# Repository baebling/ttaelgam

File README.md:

# ttaelgam
custom keyboard design

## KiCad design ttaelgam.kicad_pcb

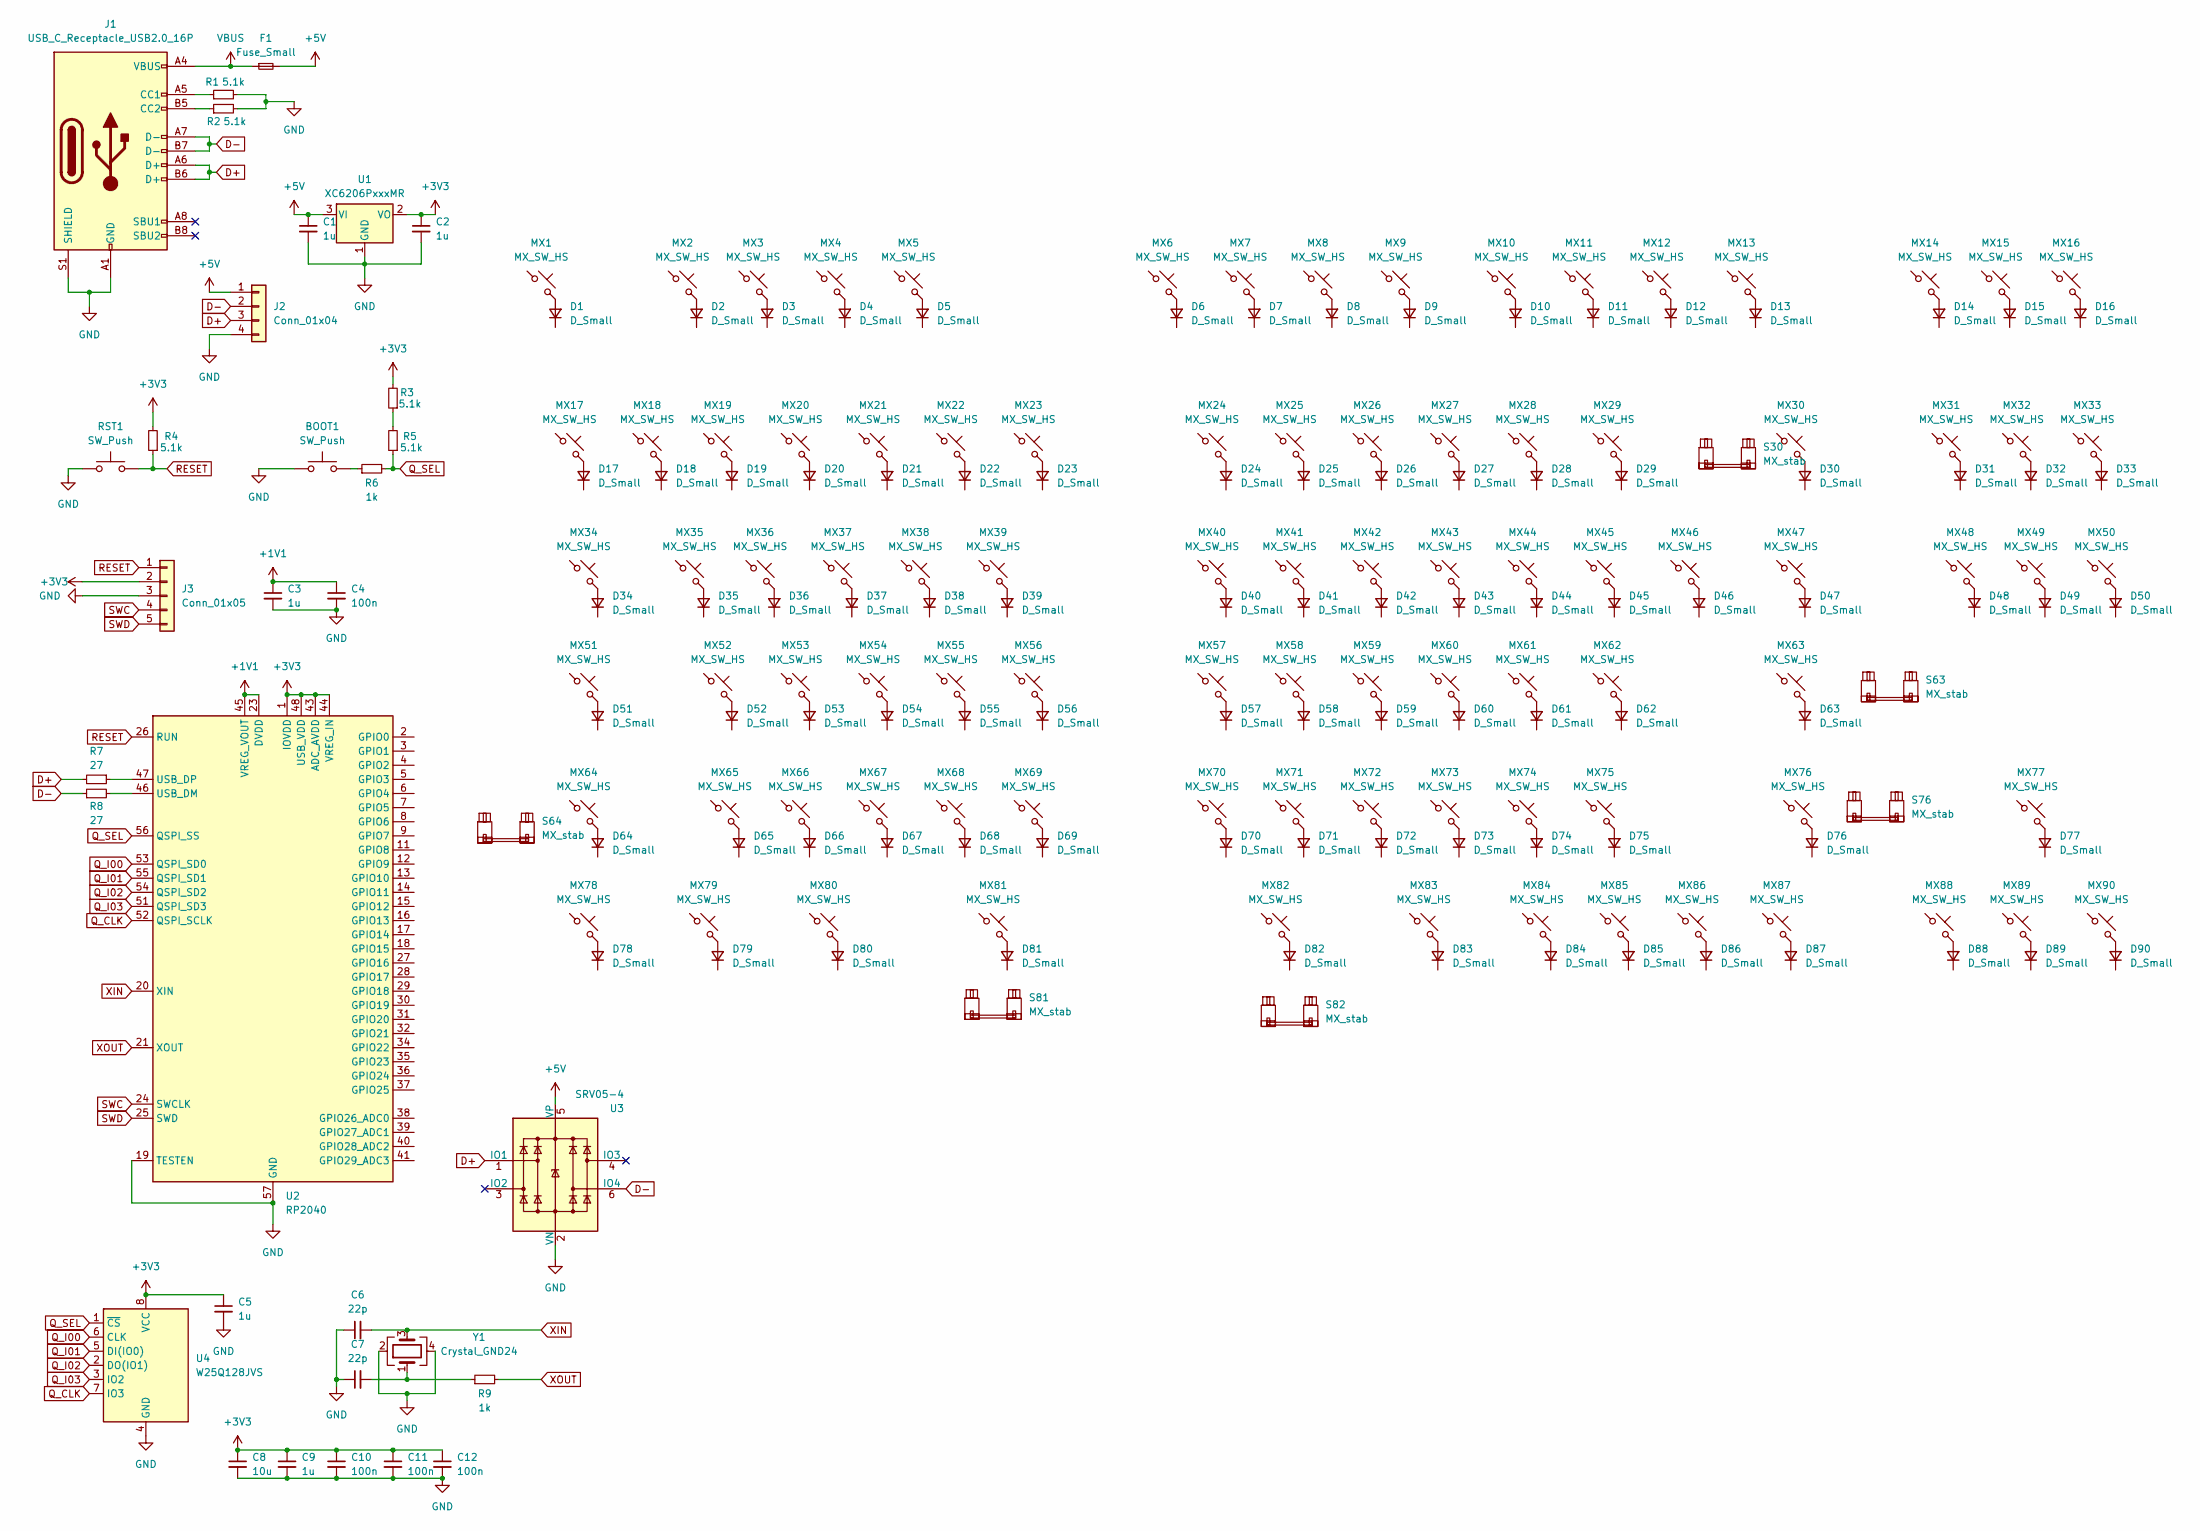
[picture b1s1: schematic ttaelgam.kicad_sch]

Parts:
BOOT1: SW_Push; SW_SPST_TL3342
C1, C2, C3, C5, C9: 1u; C_0402_1005Metric
C4, C10, C11, C12: 100n; C_0402_1005Metric
C6, C7: 22p; C_0402_1005Metric
C8: 10u; C_0603_1608Metric
D1, D2, D3, D4, D5, D6, D7, D8, D9, D10, D11, D12, D13, D14, D15, D16, D17, D18, D19, D20, D21, D22, D23, D24, D25, D26, D27, D28, D29, D30, D31, D32, D33, D34, D35, D36, D37, D38, D39, D40, D41, D42, D43, D44, D45, D46, D47, D48, D49, D50, D51, D52, D53, D54, D55, D56, D57, D58, D59, D60, D61, D62, D63, D64, D65, D66, D67, D68, D69, D70, D71, D72, D73, D74, D75, D76, D77, D78, D79, D80, D81, D82, D83, D84, D85, D86, D87, D88, D89, D90: D_Small; D_SOD-123
F1: Fuse_Small; Fuse_1206_3216Metric
J1: USB_C_Receptacle_USB2.0_16P; USB_C_Receptacle_HRO_TYPE-C-31-M-12
J2: Conn_01x04; JST_SH_SM04B-SRSS-TB_1x04-1MP_P1.00mm_Horizontal
J3: Conn_01x05; PinHeader_1x05_P2.54mm_Vertical
MX1, MX2, MX3, MX4, MX5, MX6, MX7, MX8, MX9, MX10, MX11, MX12, MX13, MX14, MX15, MX16, MX17, MX18, MX19, MX20, MX21, MX22, MX23, MX24, MX25, MX26, MX27, MX28, MX29, MX30, MX31, MX32, MX33, MX35, MX36, MX37, MX38, MX39, MX40, MX41, MX42, MX43, MX44, MX45, MX46, MX48, MX49, MX50, MX52, MX53, MX54, MX55, MX56, MX57, MX58, MX59, MX60, MX61, MX62, MX63, MX64, MX65, MX66, MX67, MX68, MX69, MX70, MX71, MX72, MX73, MX74, MX75, MX76, MX77, MX81, MX82, MX84, MX85, MX86, MX87, MX88, MX89, MX90: MX_SW_HS; SW_MX_HS_CPG151101S11_1u
MX34, MX47: MX_SW_HS; SW_MX_HS_CPG151101S11_1.5u
MX51: MX_SW_HS; SW_MX_HS_CPG151101S11_1.75u_STP_1.25
MX78, MX79, MX80, MX83: MX_SW_HS; SW_MX_HS_CPG151101S11_1.25u
R1, R2, R3, R4, R5: 5.1k; R_0402_1005Metric
R6, R9: 1k; R_0402_1005Metric
R7, R8: 27; R_0402_1005Metric
RST1: SW_Push; SW_SPST_TL3342
S30: MX_stab; STAB_MX_2u
S63, S64: MX_stab; STAB_MX_2.25u
S76, S81: MX_stab; STAB_MX_2.75u
S82: MX_stab; STAB_MX_3u
U1: XC6206PxxxMR; SOT-23-3
U2: RP2040; QFN-56-1EP_7x7mm_P0.4mm_EP3.2x3.2mm
U3: SRV05-4; SOT-23-6
U4: W25Q128JVS; SOIC-8_5.23x5.23mm_P1.27mm
Y1: Crystal_GND24; Crystal_SMD_3225-4Pin_3.2x2.5mm

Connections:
+1V1: C3.1, C4.1, U2.23 (DVDD), U2.45 (VREG_VOUT), U2.50 (DVDD)
+3V3: C2.1, C5.1, C8.1, C9.1, C10.1, C11.1, C12.1, J3.2, R3.2, R4.2, U1.2 (VO), U2.1 (IOVDD), U2.10 (IOVDD), U2.22 (IOVDD), U2.33 (IOVDD), U2.42 (IOVDD), U2.43 (ADC_AVDD), U2.44 (VREG_IN), U2.48 (USB_VDD), U2.49 (IOVDD), U4.8 (VCC)
+5V: C1.1, F1.2, J2.1, U1.3 (VI), U3.5 (VP)
D+: J1.A6 (D+), J1.B6 (D+), J2.3, R7.2, U3.1 (IO1)
D-: J1.A7 (D-), J1.B7 (D-), J2.2, R8.1, U3.6 (IO4)
GND: BOOT1.1, C1.2, C2.2, C3.2, C4.2, C5.2, C6.1, C7.1, C8.2, C9.2, C10.2, C11.2, C12.2, J1.A1 (GND), J1.A12 (GND), J1.B1 (GND), J1.B12 (GND), J1.S1 (SHIELD), J2.4, J3.3, R1.2, R2.2, RST1.1, U1.1 (GND), U2.19 (TESTEN), U2.57 (GND), U3.2 (VN), U4.4 (GND), Y1.2, Y1.4
unnamed: BOOT1.2, R6.1
unnamed: C7.2, R9.1, Y1.1
unnamed: D1.2 (A), MX1.2
unnamed: D2.2 (A), MX2.2
unnamed: D3.2 (A), MX3.2
unnamed: D4.2 (A), MX4.2
unnamed: D5.2 (A), MX5.2
unnamed: D6.2 (A), MX6.2
unnamed: D7.2 (A), MX7.2
unnamed: D8.2 (A), MX8.2
unnamed: D9.2 (A), MX9.2
unnamed: D10.2 (A), MX10.2
unnamed: D11.2 (A), MX11.2
unnamed: D12.2 (A), MX12.2
unnamed: D13.2 (A), MX13.2
unnamed: D14.2 (A), MX14.2
unnamed: D15.2 (A), MX15.2
unnamed: D16.2 (A), MX16.2
unnamed: D17.2 (A), MX17.2
unnamed: D18.2 (A), MX18.2
unnamed: D19.2 (A), MX19.2
unnamed: D20.2 (A), MX20.2
unnamed: D21.2 (A), MX21.2
unnamed: D22.2 (A), MX22.2
unnamed: D23.2 (A), MX23.2
unnamed: D24.2 (A), MX24.2
unnamed: D25.2 (A), MX25.2
unnamed: D26.2 (A), MX26.2
unnamed: D27.2 (A), MX27.2
unnamed: D28.2 (A), MX28.2
unnamed: D29.2 (A), MX29.2
unnamed: D30.2 (A), MX30.2
unnamed: D31.2 (A), MX31.2
unnamed: D32.2 (A), MX32.2
unnamed: D33.2 (A), MX33.2
unnamed: D34.2 (A), MX34.2
unnamed: D35.2 (A), MX35.2
unnamed: D36.2 (A), MX36.2
unnamed: D37.2 (A), MX37.2
unnamed: D38.2 (A), MX38.2
unnamed: D39.2 (A), MX39.2
unnamed: D40.2 (A), MX40.2
unnamed: D41.2 (A), MX41.2
unnamed: D42.2 (A), MX42.2
unnamed: D43.2 (A), MX43.2
unnamed: D44.2 (A), MX44.2
unnamed: D45.2 (A), MX45.2
unnamed: D46.2 (A), MX46.2
unnamed: D47.2 (A), MX47.2
unnamed: D48.2 (A), MX48.2
unnamed: D49.2 (A), MX49.2
unnamed: D50.2 (A), MX50.2
unnamed: D51.2 (A), MX51.2
unnamed: D52.2 (A), MX52.2
unnamed: D53.2 (A), MX53.2
unnamed: D54.2 (A), MX54.2
unnamed: D55.2 (A), MX55.2
unnamed: D56.2 (A), MX56.2
unnamed: D57.2 (A), MX57.2
unnamed: D58.2 (A), MX58.2
unnamed: D59.2 (A), MX59.2
unnamed: D60.2 (A), MX60.2
unnamed: D61.2 (A), MX61.2
unnamed: D62.2 (A), MX62.2
unnamed: D63.2 (A), MX63.2
unnamed: D64.2 (A), MX64.2
unnamed: D65.2 (A), MX65.2
unnamed: D66.2 (A), MX66.2
unnamed: D67.2 (A), MX67.2
unnamed: D68.2 (A), MX68.2
unnamed: D69.2 (A), MX69.2
unnamed: D70.2 (A), MX70.2
unnamed: D71.2 (A), MX71.2
unnamed: D72.2 (A), MX72.2
unnamed: D73.2 (A), MX73.2
unnamed: D74.2 (A), MX74.2
unnamed: D75.2 (A), MX75.2
unnamed: D76.2 (A), MX76.2
unnamed: D77.2 (A), MX77.2
unnamed: D78.2 (A), MX78.2
unnamed: D79.2 (A), MX79.2
unnamed: D80.2 (A), MX80.2
unnamed: D81.2 (A), MX81.2
unnamed: D82.2 (A), MX82.2
unnamed: D83.2 (A), MX83.2
unnamed: D84.2 (A), MX84.2
unnamed: D85.2 (A), MX85.2
unnamed: D86.2 (A), MX86.2
unnamed: D87.2 (A), MX87.2
unnamed: D88.2 (A), MX88.2
unnamed: D89.2 (A), MX89.2
unnamed: D90.2 (A), MX90.2
unnamed: J1.A5 (CC1), R1.1
unnamed: J1.B5 (CC2), R2.1
unnamed: R3.1, R5.2
unnamed: R8.2, U2.46 (USB_DM)
unnamed: R7.1, U2.47 (USB_DP)
Q_CLK: U2.52 (QSPI_SCLK), U4.7 (IO3)
Q_I00: U2.53 (QSPI_SD0), U4.6 (CLK)
Q_I01: U2.55 (QSPI_SD1), U4.5 (DI(IO0))
Q_I02: U2.54 (QSPI_SD2), U4.2 (DO(IO1))
Q_I03: U2.51 (QSPI_SD3), U4.3 (IO2)
Q_SEL: R5.1, R6.2, U2.56 (QSPI_SS), U4.1 (~CS)
RESET: J3.1, R4.1, RST1.2, U2.26 (RUN)
SWC: J3.4, U2.24 (SWCLK)
SWD: J3.5, U2.25 (SWD)
VBUS: F1.1, J1.A4 (VBUS), J1.A9 (VBUS), J1.B4 (VBUS), J1.B9 (VBUS)
XIN: C6.2, U2.20 (XIN), Y1.3
XOUT: R9.2, U2.21 (XOUT)

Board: 2 copper layers, 218 parts (212 on the bottom side), 115 nets, no tracks yet.

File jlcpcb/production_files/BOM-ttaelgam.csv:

Comment,Designator,Footprint,LCSC
W25Q128JVS,U4,SOIC-8_5.23x5.23mm_P1.27mm,C113767
1k,"R6,R9",R_0402_1005Metric,C11702
22p,"C6,C7",C_0402_1005Metric,C1555
RP2040,U2,QFN-56-1EP_7x7mm_P0.4mm_EP3.2x3.2mm,C2040
27,"R7,R8",R_0402_1005Metric,C25100
5.1k,"R3,R4,R5",R_0402_1005Metric,C25905
XC6206PxxxMR,U1,SOT-23-3,C2897477
100n,"C10,C11,C12,C13,C14,C15,C16,C4",C_0402_1005Metric,C307331
SW_Push,"BOOT1,RST1",SW_SPST_TL3342,C318884
Conn_01x05,J3,PinHeader_1x05_P2.54mm_Vertical,C358687
1u,"C1,C2,C3,C5,C9",C_0402_1005Metric,C52923
78171-0004,J4,Molex_Pico-EZmate_78171-0004_1x04-1MP_P1.20mm_Vertical,C588524
D_Small,"D1,D10,D11,D12,D13,D14,D15,D16,D17,D18,D19,D2,D20,D21,D22,D23,D24,D25,D26,D27,D28,D29,D3,D30,D31,D32,D33,D34,D35,D36,D37,D38,D39,D4,D40,D41,D42,D43,D44,D45,D46,D47,D48,D49,D5,D50,D51,D52,D53,D54,D55,D56,D57,D58,D59,D6,D60,D61,D62,D63,D64,D65,D66,D67,D68,D69,D7,D70,D71,D72,D73,D74,D75,D76,D77,D78,D79,D8,D80,D81,D82,D83,D84,D85,D86,D87,D88,D89,D9,D90",D_SOD-123,C81598
Crystal_GND24,Y1,Crystal_SMD_3225-4Pin_3.2x2.5mm,C9006
10u,C8,C_0603_1608Metric,C96446
MX_stab,S63,STAB_MX_2.25u,
MX_stab,S82,STAB_MX_3u,
MX_stab,S30,STAB_MX_2u,
MX_stab,S81,STAB_MX_2.75u,
MX_stab,S76,STAB_MX_2.75u,
MX_stab,S64,STAB_MX_2.25u,
MX_SW_HS,MX52,SW_MX_HS_CPG151101S11_1u,
MX_SW_HS,MX2,SW_MX_HS_CPG151101S11_1u,
MX_SW_HS,MX55,SW_MX_HS_CPG151101S11_1u,
MX_SW_HS,MX18,SW_MX_HS_CPG151101S11_1u,
MX_SW_HS,MX24,SW_MX_HS_CPG151101S11_1u,
MX_SW_HS,MX69,SW_MX_HS_CPG151101S11_1u,
MX_SW_HS,MX66,SW_MX_HS_CPG151101S11_1u,
MX_SW_HS,MX84,SW_MX_HS_CPG151101S11_1u,
MX_SW_HS,MX58,SW_MX_HS_CPG151101S11_1u,
MX_SW_HS,MX64,SW_MX_HS_CPG151101S11_1u,
MX_SW_HS,MX78,SW_MX_HS_CPG151101S11_1.25u,
MX_SW_HS,MX73,SW_MX_HS_CPG151101S11_1u,
MX_SW_HS,MX61,SW_MX_HS_CPG151101S11_1u,
MX_SW_HS,MX63,SW_MX_HS_CPG151101S11_1u,
MX_SW_HS,MX89,SW_MX_HS_CPG151101S11_1u,
MX_SW_HS,MX22,SW_MX_HS_CPG151101S11_1u,
MX_SW_HS,MX44,SW_MX_HS_CPG151101S11_1u,
MX_SW_HS,MX67,SW_MX_HS_CPG151101S11_1u,
MX_SW_HS,MX74,SW_MX_HS_CPG151101S11_1u,
MX_SW_HS,MX36,SW_MX_HS_CPG151101S11_1u,
MX_SW_HS,MX39,SW_MX_HS_CPG151101S11_1u,
MX_SW_HS,MX88,SW_MX_HS_CPG151101S11_1u,
MX_SW_HS,MX19,SW_MX_HS_CPG151101S11_1u,
MX_SW_HS,MX3,SW_MX_HS_CPG151101S11_1u,
MX_SW_HS,MX71,SW_MX_HS_CPG151101S11_1u,
MX_SW_HS,MX27,SW_MX_HS_CPG151101S11_1u,
MX_SW_HS,MX5,SW_MX_HS_CPG151101S11_1u,
MX_SW_HS,MX76,SW_MX_HS_CPG151101S11_1u,
MX_SW_HS,MX9,SW_MX_HS_CPG151101S11_1u,
MX_SW_HS,MX13,SW_MX_HS_CPG151101S11_1u,
MX_SW_HS,MX21,SW_MX_HS_CPG151101S11_1u,
MX_SW_HS,MX33,SW_MX_HS_CPG151101S11_1u,
MX_SW_HS,MX26,SW_MX_HS_CPG151101S11_1u,
MX_SW_HS,MX12,SW_MX_HS_CPG151101S11_1u,
MX_SW_HS,MX16,SW_MX_HS_CPG151101S11_1u,
MX_SW_HS,MX34,SW_MX_HS_CPG151101S11_1.5u,
MX_SW_HS,MX40,SW_MX_HS_CPG151101S11_1u,
MX_SW_HS,MX82,SW_MX_HS_CPG151101S11_1u,
MX_SW_HS,MX43,SW_MX_HS_CPG151101S11_1u,
MX_SW_HS,MX30,SW_MX_HS_CPG151101S11_1u,
MX_SW_HS,MX7,SW_MX_HS_CPG151101S11_1u,
MX_SW_HS,MX68,SW_MX_HS_CPG151101S11_1u,
MX_SW_HS,MX17,SW_MX_HS_CPG151101S11_1u,
MX_SW_HS,MX35,SW_MX_HS_CPG151101S11_1u,
MX_SW_HS,MX4,SW_MX_HS_CPG151101S11_1u,
MX_SW_HS,MX8,SW_MX_HS_CPG151101S11_1u,
MX_SW_HS,MX1,SW_MX_HS_CPG151101S11_1u,
MX_SW_HS,MX49,SW_MX_HS_CPG151101S11_1u,
MX_SW_HS,MX83,SW_MX_HS_CPG151101S11_1.25u,
MX_SW_HS,MX48,SW_MX_HS_CPG151101S11_1u,
MX_SW_HS,MX62,SW_MX_HS_CPG151101S11_1u,
MX_SW_HS,MX75,SW_MX_HS_CPG151101S11_1u,
MX_SW_HS,MX25,SW_MX_HS_CPG151101S11_1u,
MX_SW_HS,MX32,SW_MX_HS_CPG151101S11_1u,
MX_SW_HS,MX15,SW_MX_HS_CPG151101S11_1u,
MX_SW_HS,MX41,SW_MX_HS_CPG151101S11_1u,
MX_SW_HS,MX86,SW_MX_HS_CPG151101S11_1u,
MX_SW_HS,MX60,SW_MX_HS_CPG151101S11_1u,
MX_SW_HS,MX10,SW_MX_HS_CPG151101S11_1u,
MX_SW_HS,MX81,SW_MX_HS_CPG151101S11_1u,
MX_SW_HS,MX65,SW_MX_HS_CPG151101S11_1u,
MX_SW_HS,MX14,SW_MX_HS_CPG151101S11_1u,
MX_SW_HS,MX38,SW_MX_HS_CPG151101S11_1u,
MX_SW_HS,MX46,SW_MX_HS_CPG151101S11_1u,
MX_SW_HS,MX53,SW_MX_HS_CPG151101S11_1u,
MX_SW_HS,MX29,SW_MX_HS_CPG151101S11_1u,
MX_SW_HS,MX23,SW_MX_HS_CPG151101S11_1u,
MX_SW_HS,MX31,SW_MX_HS_CPG151101S11_1u,
MX_SW_HS,MX37,SW_MX_HS_CPG151101S11_1u,
MX_SW_HS,MX42,SW_MX_HS_CPG151101S11_1u,
MX_SW_HS,MX90,SW_MX_HS_CPG151101S11_1u,
MX_SW_HS,MX45,SW_MX_HS_CPG151101S11_1u,
MX_SW_HS,MX20,SW_MX_HS_CPG151101S11_1u,
MX_SW_HS,MX85,SW_MX_HS_CPG151101S11_1u,
MX_SW_HS,MX50,SW_MX_HS_CPG151101S11_1u,
MX_SW_HS,MX54,SW_MX_HS_CPG151101S11_1u,
MX_SW_HS,MX11,SW_MX_HS_CPG151101S11_1u,
MX_SW_HS,MX80,SW_MX_HS_CPG151101S11_1.25u,
MX_SW_HS,MX28,SW_MX_HS_CPG151101S11_1u,
MX_SW_HS,MX57,SW_MX_HS_CPG151101S11_1u,
MX_SW_HS,MX59,SW_MX_HS_CPG151101S11_1u,
MX_SW_HS,MX47,SW_MX_HS_CPG151101S11_1.5u,
MX_SW_HS,MX6,SW_MX_HS_CPG151101S11_1u,
MX_SW_HS,MX79,SW_MX_HS_CPG151101S11_1.25u,
MX_SW_HS,MX56,SW_MX_HS_CPG151101S11_1u,
MX_SW_HS,MX70,SW_MX_HS_CPG151101S11_1u,
MX_SW_HS,MX77,SW_MX_HS_CPG151101S11_1u,
MX_SW_HS,MX72,SW_MX_HS_CPG151101S11_1u,
MX_SW_HS,MX51,SW_MX_HS_CPG151101S11_1.75u_STP_1.25,
MX_SW_HS,MX87,SW_MX_HS_CPG151101S11_1u,

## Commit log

2024-08-04 Add footprint libraries
2024-08-04 2408041538
2024-08-04 202408042026
2024-08-04 0804over
2024-08-07 20240807
2024-08-08 20240808
2024-08-10 0810
2024-08-17 0817
2024-08-23 0823
2024-08-27 0827
2024-09-01 0901
2024-10-17 241017
2024-10-19 241019
2024-10-19 241019-1
2025-01-31 250131
2025-12-17 Problem
    Problem
    -Crystal Unit 12MHz
    -Flash wiring error
